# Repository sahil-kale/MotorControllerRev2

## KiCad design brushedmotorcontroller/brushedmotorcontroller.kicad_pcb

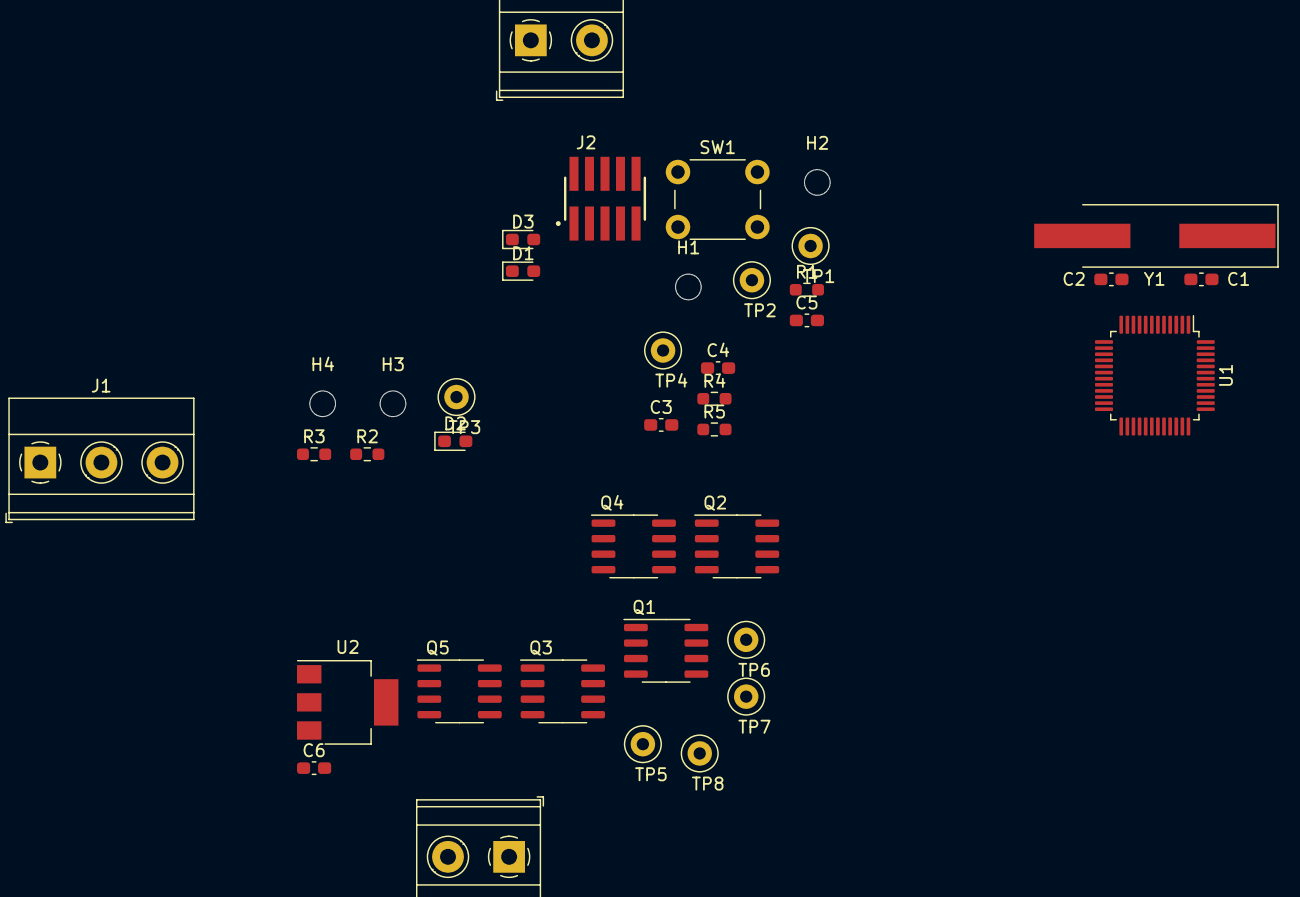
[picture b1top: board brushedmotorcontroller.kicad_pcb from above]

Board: 2 copper layers, 39 parts (0 on the bottom side), 23 nets, no tracks yet.

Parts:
C1, C2, C3, C4, C5: 0.1uF; C_0603_1608Metric_Pad1.08x0.95mm_HandSolder
C6: 1uF; C_0603_1608Metric_Pad1.08x0.95mm_HandSolder
D1: LED_R; LED_0603_1608Metric_Pad1.05x0.95mm_HandSolder
D2: LED_B; LED_0603_1608Metric_Pad1.05x0.95mm_HandSolder
D3: LED_G; LED_0603_1608Metric_Pad1.05x0.95mm_HandSolder
H1, H2, H3, H4: MountingHole; MountingHole_2.1mm
J1: Screw_Terminal_01x03; TerminalBlock_Phoenix_MKDS-1,5-3_1x03_P5.00mm_Horizontal
J2: PROG; FTSH-105-01-F
J3, J4: Screw_Terminal_01x02; TerminalBlock_Phoenix_MKDS-1,5-2_1x02_P5.00mm_Horizontal
Q1, Q2, Q3, Q4, Q5: Q_NMOS_DGS; SI4776DY
R1, R2, R3: 330; R_0603_1608Metric_Pad0.98x0.95mm_HandSolder
R4: 10k; R_0603_1608Metric_Pad0.98x0.95mm_HandSolder
R5: 2k; R_0603_1608Metric_Pad0.98x0.95mm_HandSolder
SW1: SW_Push; SW_PUSH_6mm
TP1, TP2, TP3, TP4, TP5, TP6, TP7, TP8: TestPoint; TestPoint_Loop_D1.80mm_Drill1.0mm_Beaded
U1: STM32F030C8Tx; LQFP-48_7x7mm_P0.5mm
U2: LD1117S33TR_SOT223; SOT-223-3_TabPin2
Y1: 8MHz; Crystal_SMD_HC49-SD_HandSoldering

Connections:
+3V3: C4.1, C5.2, J2.1, U1.1, U1.9, U1.24, U1.48, U2.2
/LED_B: R2.1, U1.27
/LED_G: R3.1, U1.28
/LED_R: R1.1, U1.26
/PF0: C1.2, U1.5, Y1.1
/PF1: C2.2, U1.6, Y1.2
/PWM_IN: J1.3, TP1.1, U1.12
/RST: C3.2, J2.10, SW1.2, TP2.1, U1.7
/SWCLK: J2.4, TP3.1, U1.37
/SWDIO: J2.2, TP4.1, U1.34
/VBUS_ADC: R4.2, R5.1, U1.10
/switching/MOTOR+: J4.1, Q2.3, Q3.1
/switching/MOTOR-: J4.2, Q4.3, Q5.1
GND: C1.1, C2.1, C3.1, C4.2, C5.1, C6.2, D1.1, D2.1, D3.1, J1.1, J2.3, J2.5, J2.9, Q1.3, Q3.3, Q5.3, R5.2, SW1.1, U1.8, U1.23, U1.44, U1.47, U2.1
unnamed: D1.2, R1.2
unnamed: D2.2, R2.2
unnamed: D3.2, R3.2
unnamed: J3.1, Q1.1
TIM1_CH1: Q2.2, TP5.1, U1.29
TIM1_CH2: Q3.2, TP6.1, U1.30
TIM1_CH3: Q4.2, TP7.1, U1.31
TIM1_CH4: Q5.2, TP8.1, U1.32
VBUS: C6.1, J3.2, Q1.2, Q2.1, Q4.1, R4.1, U2.3

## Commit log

2021-09-30 Stuff
